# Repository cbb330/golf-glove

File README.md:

# Golf Glove
Senior Design Repository

## Firmware Quick-Reference
The Golf Glove device uses Bluetooth Low Energy (minimum BT v4.0) using the [Generic ATTribute](https://en.wikipedia.org/wiki/Bluetooth_Low_Energy#GATT_operations) (GATT) profile, an application layer protocol.

* [Golf Glove GATT Service Reference](firmware/GATT.md)

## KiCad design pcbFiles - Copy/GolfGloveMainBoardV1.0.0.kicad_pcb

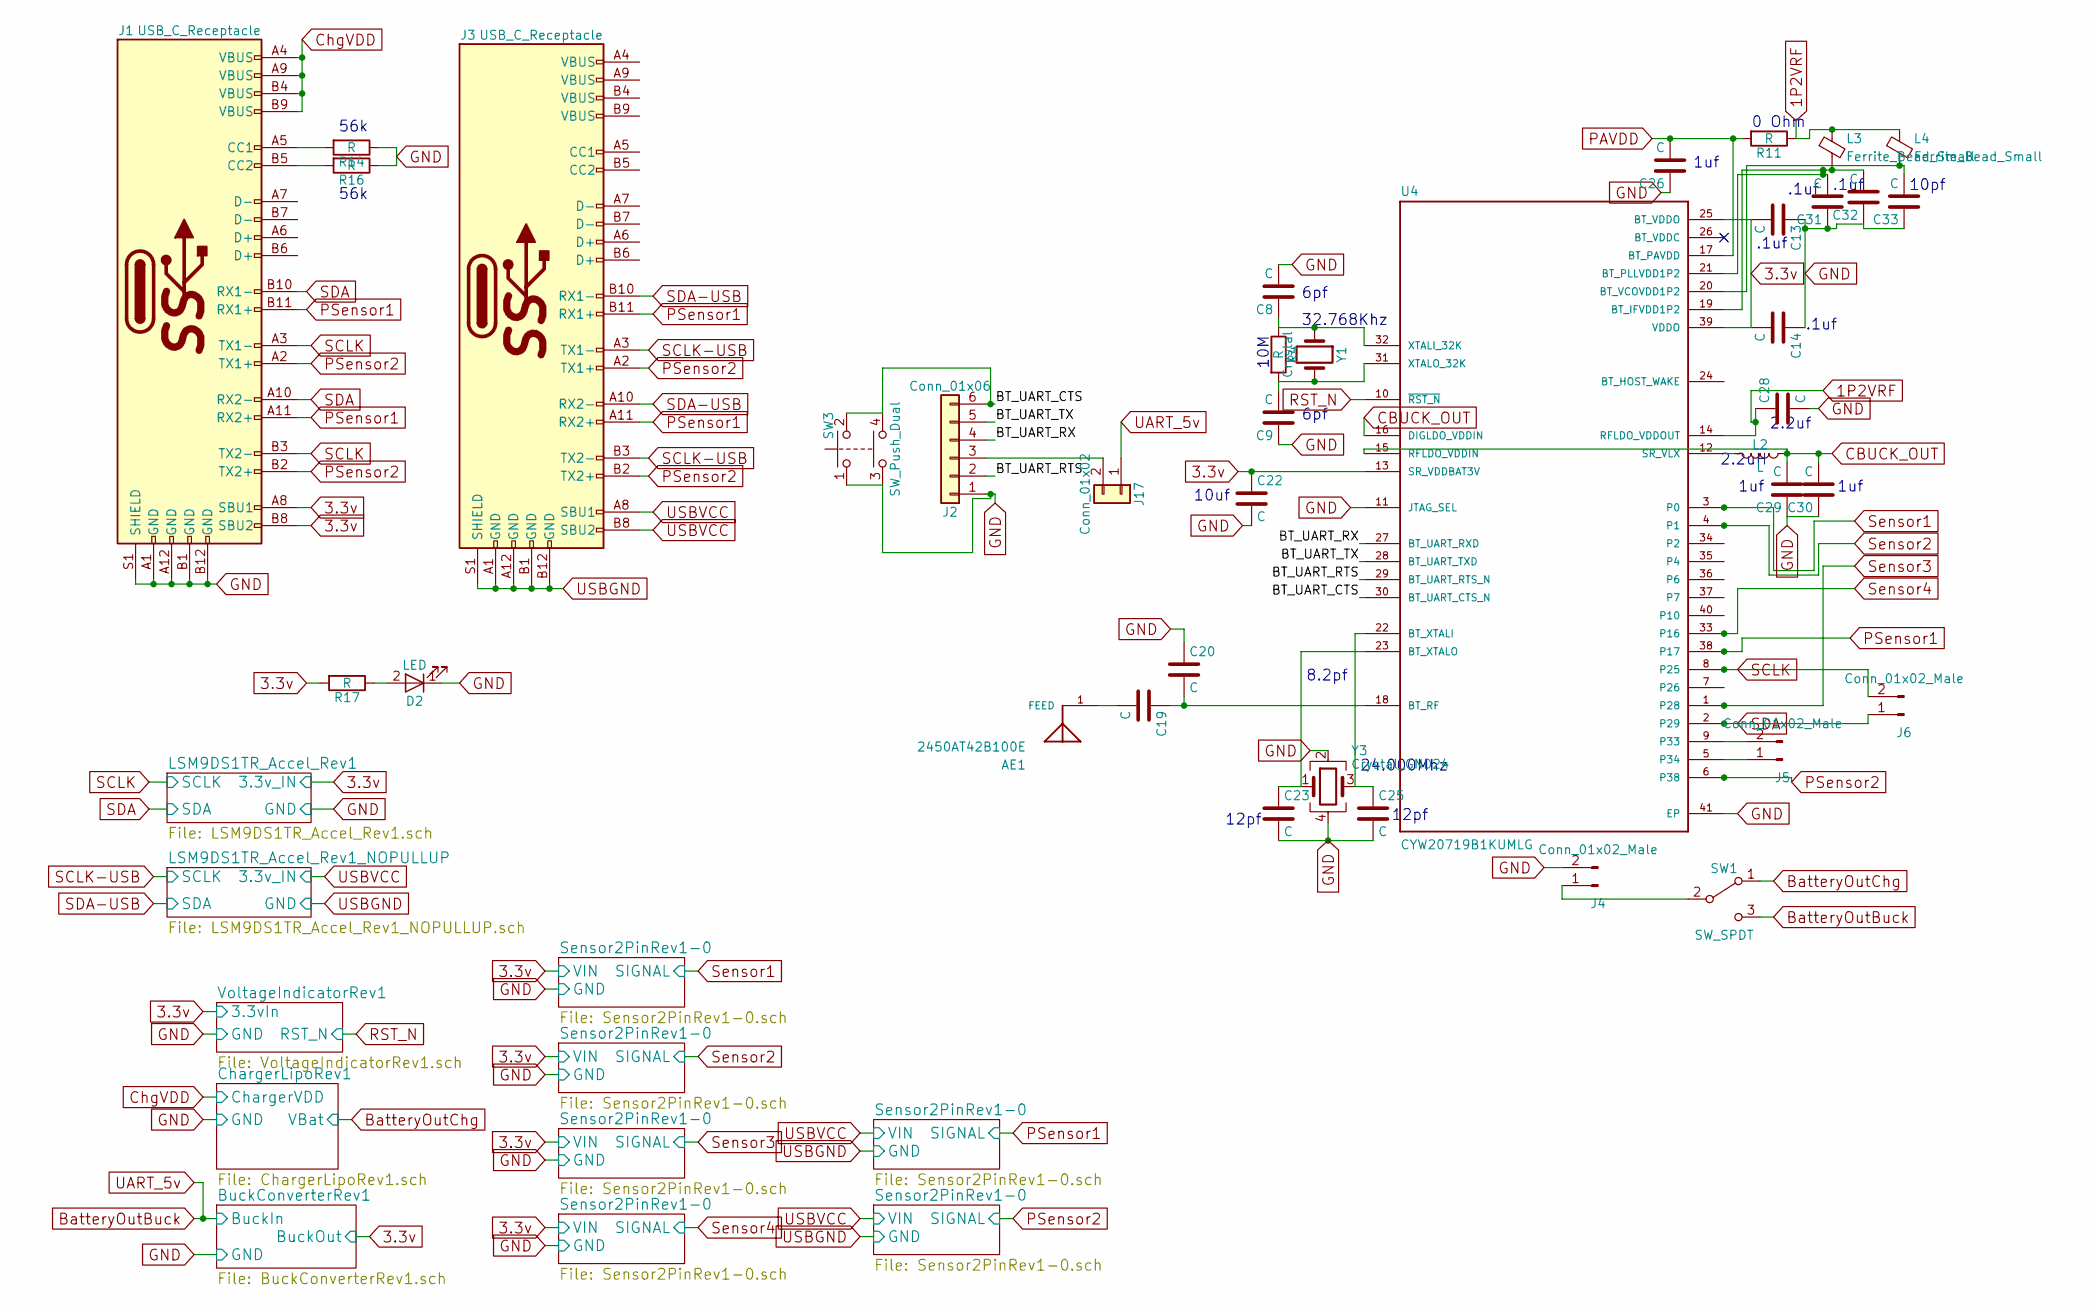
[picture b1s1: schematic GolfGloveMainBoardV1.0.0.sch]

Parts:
AE1: 2450AT42B100E; XCVR_2450AT42B100E
C8, C9, C13, C14, C19, C20, C22, C23, C25, C26, C28, C29, C30, C31, C32, C33: C; C_0402
D2: LED; C_0603
J1, J3: USB_C_Receptacle; USB_C_Receptacle_Amphenol_12401548E4-2A
J2: Conn_01x06; Pin_Header_Straight_1x06_Pitch2.54mm
J4, J5, J6: Conn_01x02_Male; Pin_Header_Straight_1x02_Pitch2.54mm
J17: Conn_01x02; Pin_Header_Straight_1x02_Pitch2.54mm
L2: L; L_0402
L3, L4: Ferrite_Bead_Small; R_0603
R4, R11, R14, R16, R17: R; R_0402
SW1: SW_SPDT; SW_SPDT_PCM12
SW3: SW_Push_Dual; SW_PUSH_6mm
U4: CYW20719B1KUMLG; QFN40P500X500X60-41N
Y1: Crystal; Crystal_SMD_3215-2pin_3.2x1.5mm
Y3: Crystal_GND24; Crystal_SMD_2016-4pin_2.0x1.6mm

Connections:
1P2VRF: C28.1, L3.1, L4.1, R11.1, U4.14 (RFLDO_VDDOUT)
3.3v: C13.2, C14.2, C22.1, J1.A8 (SBU1), J1.B8 (SBU2), R17.2, U4.13 (SR_VDDBAT3V), U4.25 (BT_VDDO), U4.39 (VDDO); also elsewhere on the board
/BT_UART_CTS: J2.6, SW3.2, SW3.4, U4.30 (BT_UART_CTS_N)
/BT_UART_RTS: J2.2, U4.29 (BT_UART_RTS_N)
/BT_UART_RX: J2.4, U4.27 (BT_UART_RXD)
/BT_UART_TX: J2.5, U4.28 (BT_UART_TXD)
BatteryOutBuck: J17.1, SW1.3 (C); also elsewhere on the board
BatteryOutChg: SW1.1 (A); also elsewhere on the board
CBUCK_OUT: C29.2, C30.2, L2.1, U4.15 (RFLDO_VDDIN), U4.16 (DIGLDO_VDDIN)
ChgVDD: J1.A4 (VBUS), J1.A9 (VBUS), J1.B4 (VBUS), J1.B9 (VBUS); also elsewhere on the board
GND: C8.2, C9.1, C13.1, C14.1, C20.1, C22.2, C23.2, C25.2, C26.1, C28.2, C29.1, C30.1, C31.1, C32.1, C33.1, D2.1 (K), J1.A1 (GND), J1.A12 (GND), J1.B1 (GND), J1.B12 (GND), J1.S1 (SHIELD), J2.1, J4.2, R14.1, R16.1, SW3.1, SW3.3, U4.11 (JTAG_SEL), U4.41 (EP), Y3.2, Y3.4; also elsewhere on the board
unnamed: AE1.1, C19.2
unnamed: C8.1, R4.1, U4.32 (XTALI_32K), Y1.1
unnamed: C9.2, R4.2, U4.31 (XTALO_32K), Y1.2
unnamed: C19.1, C20.2, U4.18 (BT_RF)
unnamed: C23.1, U4.23 (BT_XTALO), Y3.1
unnamed: C25.1, U4.22 (BT_XTALI), Y3.3
unnamed: C31.2, C32.2, L3.2, U4.19 (BT_IFVDD1P2), U4.21 (BT_PLLVDD1P2)
unnamed: C33.2, L4.2, U4.20 (BT_VCOVDD1P2)
unnamed: D2.2 (A), R17.1
unnamed: J1.A5 (CC1), R14.2
unnamed: J1.B5 (CC2), R16.2
unnamed: J4.1, SW1.2 (B)
unnamed: J5.1, U4.5 (P34)
unnamed: J5.2, U4.9 (P33)
unnamed: J2.3, J17.2
unnamed: L2.2, U4.12 (SR_VLX)
PAVDD: C26.2, R11.2, U4.17 (BT_PAVDD)
PSensor1: J1.A11 (RX2+), J1.B11 (RX1+), J3.A11 (RX2+), J3.B11 (RX1+), U4.38 (P17); also elsewhere on the board
PSensor2: J1.A2 (TX1+), J1.B2 (TX2+), J3.A2 (TX1+), J3.B2 (TX2+), U4.6 (P38); also elsewhere on the board
SCLK: J1.A3 (TX1-), J1.B3 (TX2-), J6.2, U4.8 (P25); also elsewhere on the board
SCLK-USB: J3.A3 (TX1-), J3.B3 (TX2-); also elsewhere on the board
SDA: J1.A10 (RX2-), J1.B10 (RX1-), J6.1, U4.2 (P29); also elsewhere on the board
SDA-USB: J3.A10 (RX2-), J3.B10 (RX1-); also elsewhere on the board
Sensor1: U4.3 (P0); also elsewhere on the board
Sensor2: U4.4 (P1); also elsewhere on the board
Sensor3: U4.1 (P28); also elsewhere on the board
Sensor4: U4.33 (P16); also elsewhere on the board
USBGND: J3.A1 (GND), J3.A12 (GND), J3.B1 (GND), J3.B12 (GND), J3.S1 (SHIELD); also elsewhere on the board
USBVCC: J3.A8 (SBU1), J3.B8 (SBU2); also elsewhere on the board

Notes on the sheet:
8.2pf
12pf
10uf
6pf
1uf
.1uf
10pf
2.2uf
2.2uH
0 Ohm
10M
32.768Khz
24.000Mhz
56k

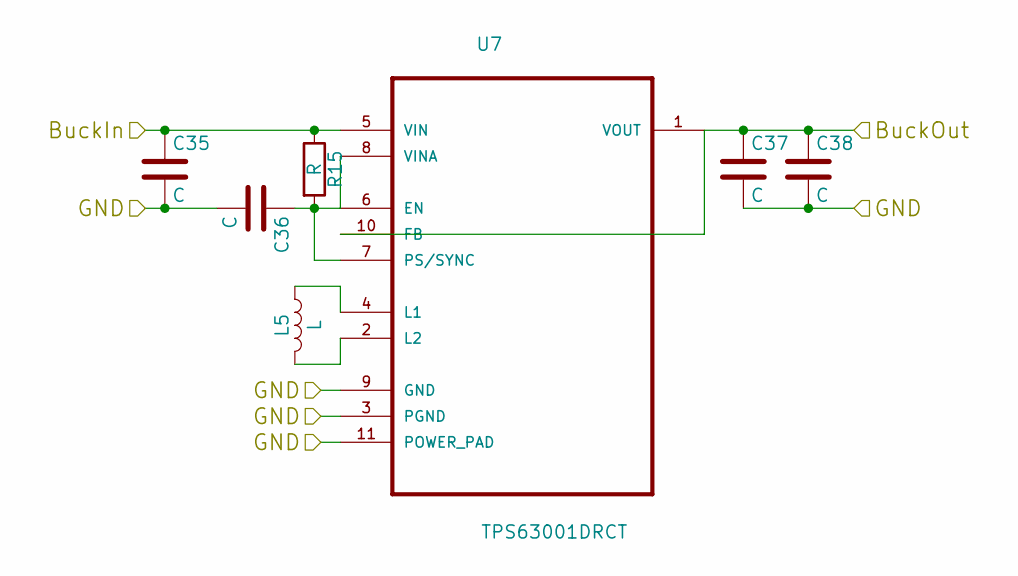
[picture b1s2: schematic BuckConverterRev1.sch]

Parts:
C35, C36, C37, C38: C; C_0402
L5: L; L_0603
R15: R; R_0402
U7: TPS63001DRCT; SON50P300X300X100-11N

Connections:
BatteryOutBuck: C35.1, R15.1, U7.5 (VIN); also elsewhere on the board
GND: C35.2, C36.2, C37.2, C38.2, U7.3 (PGND), U7.9 (GND), U7.11 (POWER_PAD); also elsewhere on the board
unnamed: C36.1, R15.2, U7.6 (EN), U7.7 (PS/SYNC), U7.8 (VINA)
unnamed 25: C37.1, C38.1, U7.1 (VOUT), U7.10 (FB); also elsewhere on the board
unnamed: L5.1, U7.4 (L1)
unnamed: L5.2, U7.2 (L2)

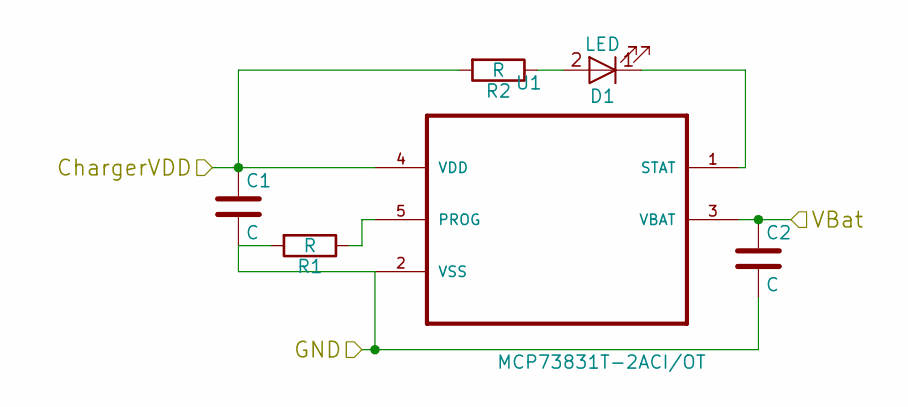
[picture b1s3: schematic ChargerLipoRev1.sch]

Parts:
C1, C2: C; C_0402
D1: LED; C_0603
R1, R2: R; R_0402
U1: MCP73831T-2ACI/OT; SOT95P280X145-5N

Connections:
BatteryOutChg: C2.1, U1.3 (VBAT); also elsewhere on the board
ChgVDD: C1.1, R2.2, U1.4 (VDD); also elsewhere on the board
GND: C1.2, C2.2, R1.2, U1.2 (VSS); also elsewhere on the board
unnamed: D1.1 (K), U1.1 (STAT)
unnamed: D1.2 (A), R2.1
unnamed: R1.1, U1.5 (PROG)

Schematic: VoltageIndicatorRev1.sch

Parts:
C3, C4: C; C_0402
J6: Screw_Terminal_01x02; Pin_Header_Straight_1x02_Pitch2.54mm
R3: R; R_0402
SW2: SW_Push; SW_DIP_x1_W8.61mm_Slide_LowProfile
U2: XC6119N16A7R-G; DFN-4

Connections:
3.3v: R3.1; also elsewhere on the board
GND: C3.2, C4.1, SW2.1, U2.3 (VSS); also elsewhere on the board
unnamed: C3.1, U2.2 (Cd/NC)

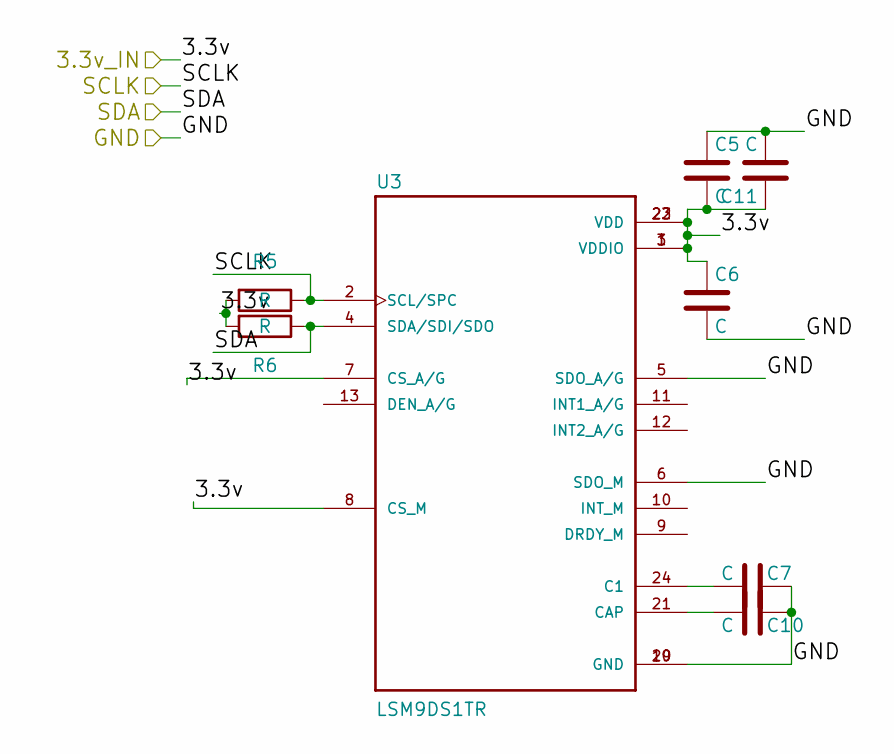
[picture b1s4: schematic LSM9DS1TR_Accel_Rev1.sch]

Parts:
C5, C6, C7, C10, C11: C; C_0402
R5, R6: R; R_0402
U3: LSM9DS1TR; PQFN43P300X350X102-24N

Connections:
3.3v: C5.2, C6.1, C11.1, R5.2, R6.2, U3.1 (VDDIO), U3.3 (VDDIO), U3.7 (CS_A/G), U3.8 (CS_M), U3.22 (VDD), U3.23 (VDD); also elsewhere on the board
GND: C5.1, C6.2, C7.1, C10.1, C11.2, U3.5 (SDO_A/G), U3.6 (SDO_M), U3.19 (GND), U3.20 (GND); also elsewhere on the board
unnamed: C7.2, U3.24 (C1)
unnamed: C10.2, U3.21 (CAP)
SCLK: R5.1, U3.2 (SCL/SPC); also elsewhere on the board
SDA: R6.1, U3.4 (SDA/SDI/SDO); also elsewhere on the board

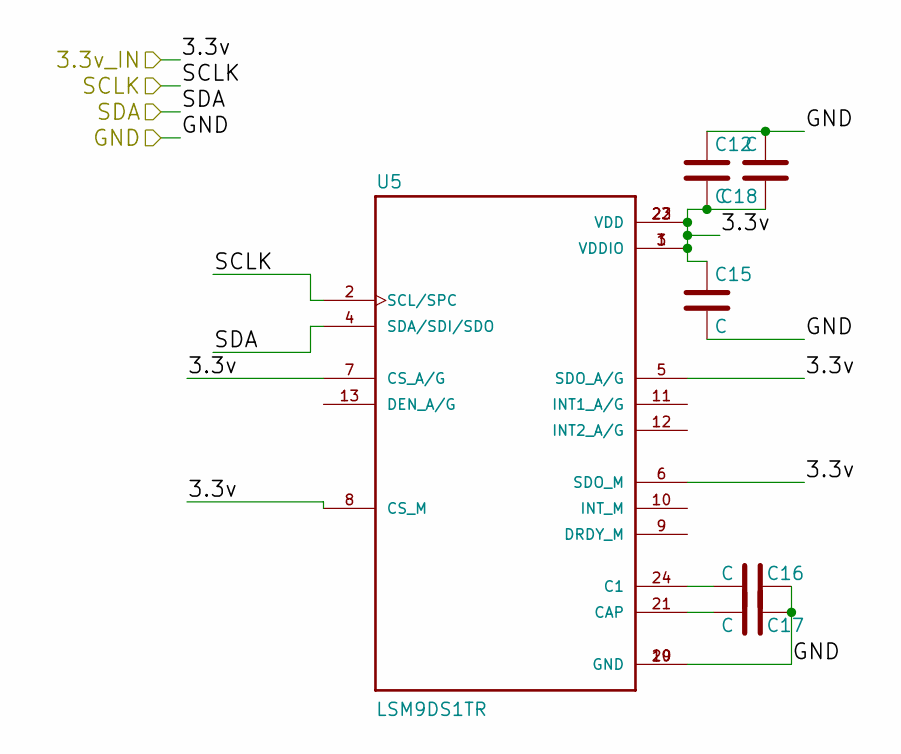
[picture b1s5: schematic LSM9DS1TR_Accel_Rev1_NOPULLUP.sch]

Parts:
C12, C15, C16, C17, C18: C; C_0402
U5: LSM9DS1TR; PQFN43P300X350X102-24N

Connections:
unnamed: C16.2, U5.24 (C1)
unnamed: C17.2, U5.21 (CAP)
SCLK-USB: U5.2 (SCL/SPC); also elsewhere on the board
SDA-USB: U5.4 (SDA/SDI/SDO); also elsewhere on the board
USBGND: C12.1, C15.2, C16.1, C17.1, C18.2, U5.19 (GND), U5.20 (GND); also elsewhere on the board
USBVCC: C12.2, C15.1, C18.1, U5.1 (VDDIO), U5.3 (VDDIO), U5.5 (SDO_A/G), U5.6 (SDO_M), U5.7 (CS_A/G), U5.8 (CS_M), U5.22 (VDD), U5.23 (VDD); also elsewhere on the board

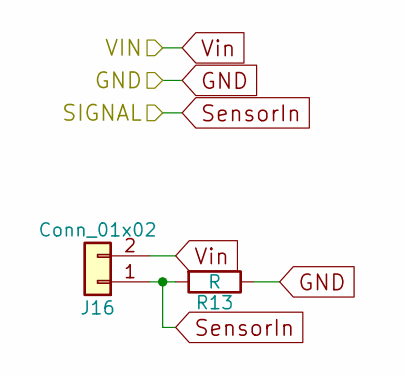
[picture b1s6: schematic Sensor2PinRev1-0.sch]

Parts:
J7: Conn_01x02; Pin_Header_Straight_1x02_Pitch2.54mm
R7: R; R_0402

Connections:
3.3v: J7.2; also elsewhere on the board
GND: R7.1; also elsewhere on the board
Sensor1: J7.1, R7.2; also elsewhere on the board

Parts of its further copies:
J8, J9, J14, J15, J16: Conn_01x02; Pin_Header_Straight_1x02_Pitch2.54mm
R8, R9, R10, R12, R13: R; R_0402

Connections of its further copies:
3.3v: J8.2, J9.2, J14.2; also elsewhere on the board
GND: R8.1, R9.1, R10.1; also elsewhere on the board
PSensor1: J15.1, R12.2; also elsewhere on the board
PSensor2: J16.1, R13.2; also elsewhere on the board
Sensor2: J8.1, R8.2; also elsewhere on the board
Sensor3: J9.1, R9.2; also elsewhere on the board
Sensor4: J14.1, R10.2; also elsewhere on the board
USBGND: R12.1, R13.1; also elsewhere on the board
USBVCC: J15.2, J16.2; also elsewhere on the board

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
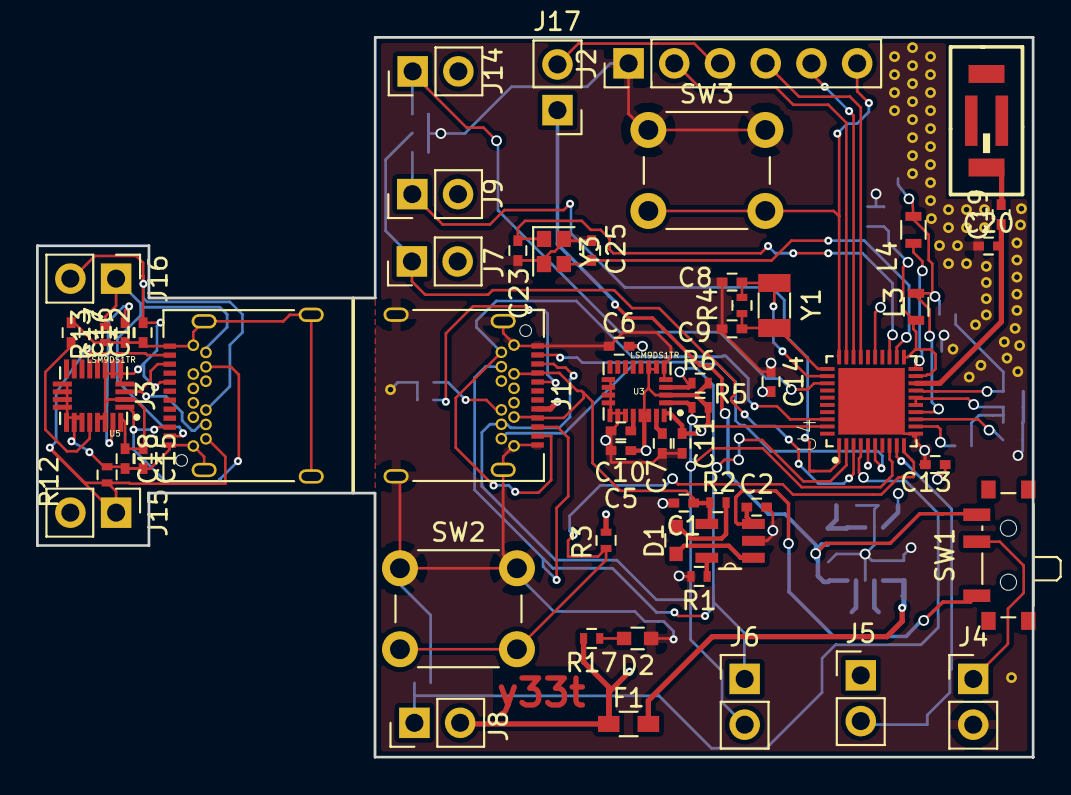
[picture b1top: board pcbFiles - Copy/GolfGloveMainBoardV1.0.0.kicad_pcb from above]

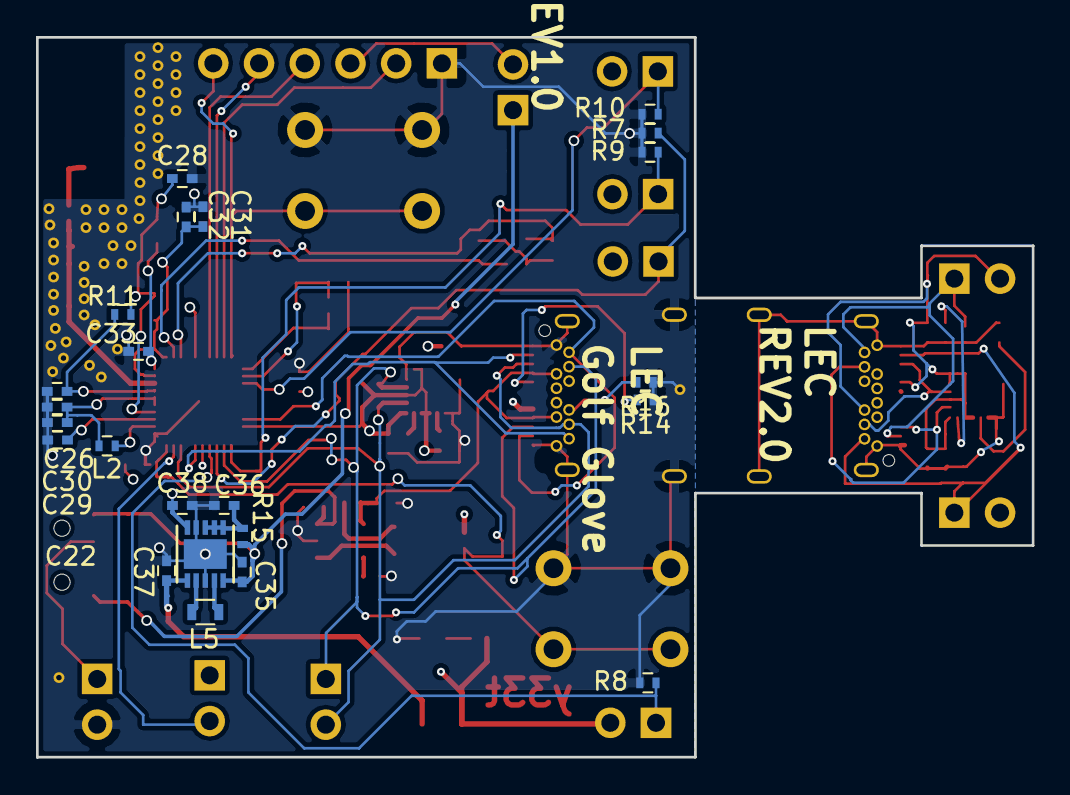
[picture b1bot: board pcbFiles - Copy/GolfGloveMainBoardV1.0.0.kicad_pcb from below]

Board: 4 copper layers, 55.3 x 40.0 mm, 80 parts (23 on the bottom side), 52 nets.

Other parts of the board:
F1: Polyfuse; R_0603_HandSoldering

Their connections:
3.3v: F1.1; also elsewhere on the board
unnamed 25: F1.2; also elsewhere on the board

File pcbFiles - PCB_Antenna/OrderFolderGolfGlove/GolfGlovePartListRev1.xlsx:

PartName | Value | Form Factor | Part Number | Brand | Price | Type | Link
C3 | .033uF | 402 |  |  |  | CAP | https://www.digikey.com/product-detail/en/kemet/C0402C333J4R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
C13 | .1uF | 402 |  |  |  | CAP | https://www.digikey.com/product-detail/en/samsung-electro-me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
C14 | .1uF | 402 |  |  |  | CAP | https://www.digikey.com/product-detail/en/samsung-electro-me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
C31 | .1uF | 402 |  |  |  | CAP | https://www.digikey.com/product-detail/en/samsung-electro-me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
C32 | .1uF | 402 |  |  |  | CAP | https://www.digikey.com/product-detail/en/samsung-electro-me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
C4 | .1uF | 402 |  |  |  | CAP | https://www.digikey.com/product-detail/en/samsung-electro-me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
C36 | .1uF | 402 |  |  |  | CAP | https://www.digikey.com/product-detail/en/samsung-electro-me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
C12 | 100nF | 402 |  |  |  | CAP | https://www.digikey.com/product-detail/en/samsung-electro-me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
C15 | 100nF | 402 |  |  |  | CAP | https://www.digikey.com/product-detail/en/samsung-electro-me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
C16 | 100nF | 402 |  |  |  | CAP | https://www.digikey.com/product-detail/en/samsung-electro-me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
C5 | 100nF | 402 |  |  |  | CAP | https://www.digikey.com/product-detail/en/samsung-electro-me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
C6 | 100nF | 402 |  |  |  | CAP | https://www.digikey.com/product-detail/en/samsung-electro-me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
C7 | 100nF | 402 |  |  |  | CAP | https://www.digikey.com/product-detail/en/samsung-electro-me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
C10 | 10nF (16V) | 402 |  |  |  | CAP | https://www.digikey.com/product-detail/en/murata-electronics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
C17 | 10nF (16V) | 402 |  |  |  | CAP | https://www.digikey.com/product-detail/en/murata-electronics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
C33 | 10pF | 402 |  |  |  | CAP | https://www.digikey.com/product-detail/en/murata-electronics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
C1 | 10uF | 402 |  |  |  | CAP | https://www.digikey.com/product-detail/en/murata-electronics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
C11 | 10uF | 402 |  |  |  | CAP | https://www.digikey.com/product-detail/en/murata-electronics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
C18 | 10uF | 402 |  |  |  | CAP | https://www.digikey.com/product-detail/en/murata-electronics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
C2 | 10uF | 402 |  |  |  | CAP | https://www.digikey.com/product-detail/en/murata-electronics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
C22 | 10uF | 402 |  |  |  | CAP | https://www.digikey.com/product-detail/en/murata-electronics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
C35 | 10uF | 402 |  |  |  | CAP | https://www.digikey.com/product-detail/en/murata-electronics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
C37 | 10uF | 402 |  |  |  | CAP | https://www.digikey.com/product-detail/en/murata-electronics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
C38 | 10uF | 402 |  |  |  | CAP | https://www.digikey.com/product-detail/en/murata-electronics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
C23 | 12pF | 402 |  |  |  | CAP | https://www.digikey.com/product-detail/en/samsung-electro-me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
C25 | 12pF | 402 |  |  |  | CAP | https://www.digikey.com/product-detail/en/samsung-electro-me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
C26 | 1uF | 402 |  |  |  | CAP | https://www.digikey.com/product-detail/en/samsung-electro-me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
C29 | 1uF | 402 |  |  |  | CAP | https://www.digikey.com/product-detail/en/samsung-electro-me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
C30 | 1uF | 402 |  |  |  | CAP | https://www.digikey.com/product-detail/en/samsung-electro-me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
C28 | 2.2uF | 402 |  |  |  | CAP | https://www.digikey.com/product-detail/en/murata-electronics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
C8 | 6pF | 402 |  |  |  | CAP | https://www.digikey.com/product-detail/en/yageo/CC0402DRNPO9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
C9 | 6pF | 402 |  |  |  | CAP | https://www.digikey.com/product-detail/en/yageo/CC0402DRNPO9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
D1 | blue LED | 603 |  | Kingbright |  | LED | https://www.digikey.com/product-detail/en/kingbright/APTD160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
J1 | USB-C | USB-C |  |  |  | CONNECTOR | https://www.ttiinc.com/content/ttiinc/en/apps/part-detail.ht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
J11 | N/A |  |  |  |  | HEADER | N/A
J12 | N/A |  |  |  |  | HEADER | N/A
J13 | N/A |  |  |  |  | HEADER | N/A
J14 | N/A |  |  |  |  | HEADER | N/A
J15 | N/A |  |  |  |  | HEADER | N/A
J16 | N/A |  |  |  |  | HEADER | N/A
J17 | N/A |  |  |  |  | HEADER | N/A
J2 | N/A |  |  |  |  | HEADER | N/A
J3 | USB-C | USB-C |  |  |  | CONNECTOR | https://www.ttiinc.com/content/ttiinc/en/apps/part-detail.ht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
J6 | N/A |  |  |  |  | HEADER | N/A
J7 | N/A |  |  |  |  | HEADER | N/A
J8 | N/A |  |  |  |  | HEADER | N/A
J9 | N/A |  |  |  |  | HEADER | N/A
L1 |  | 402 |  |  |  | INDUCTOR
L2 | 2.2uH | 402 |  |  |  | INDUCTOR | https://www.digikey.com/product-detail/en/tdk-corporation/ML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
L3 | 600@100MHz | 603 |  |  |  | FERRITE BEAD | https://www.digikey.com/product-detail/en/wurth-electronics-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
L4 | 600@100MHz | 603 |  |  |  | FERRITE BEAD | https://www.digikey.com/product-detail/en/wurth-electronics-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
L5 | 2.2uH | 603 |  |  |  | INDUCTOR | https://www.digikey.com/product-detail/en/tdk-corporation/ML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
L6 |  | 402 |  |  |  | INDUCTOR
R11 | 0 | 402 |  |  |  | RESISTOR | https://www.digikey.com/product-detail/en/stackpole-electron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
R15 | 100 | 402 |  |  |  | RESISTOR | https://www.digikey.com/product-detail/en/panasonic-electron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
R2 | 470 | 402 |  |  |  | RESISTOR | https://www.digikey.com/product-detail/en/panasonic-electron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
R5 | 10K | 402 |  |  |  | RESISTOR | https://www.digikey.com/product-detail/en/susumu/RR0510P-103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
R6 | 10K | 402 |  |  |  | RESISTOR | https://www.digikey.com/product-detail/en/susumu/RR0510P-103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
R4 | 10M | 402 |  |  |  | RESISTOR | https://www.digikey.com/product-detail/en/te-connectivity-pa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
R10 | 13.5K | 402 |  |  |  | RESISTOR | https://www.digikey.com/product-detail/en/vishay-dale/TNPW04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
R12 | 13.5K | 402 |  |  |  | RESISTOR | https://www.digikey.com/product-detail/en/vishay-dale/TNPW04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
R13 | 13.5K | 402 |  |  |  | RESISTOR | https://www.digikey.com/product-detail/en/vishay-dale/TNPW04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
R7 | 13.5K | 402 |  |  |  | RESISTOR | https://www.digikey.com/product-detail/en/vishay-dale/TNPW04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
R8 | 13.5K | 402 |  |  |  | RESISTOR | https://www.digikey.com/product-detail/en/vishay-dale/TNPW04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
R9 | 13.5K | 402 |  |  |  | RESISTOR | https://www.digikey.com/product-detail/en/vishay-dale/TNPW04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
R1 | 2k | 402 |  |  |  | RESISTOR | https://www.digikey.com/product-detail/en/yageo/RT0402BRD072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
R3 | 5.6k | 402 |  |  |  | RESISTOR | https://www.digikey.com/product-detail/en/panasonic-electron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
SW1 | SPDT PCM12 | N/A |  |  |  | SWITCH | https://www.digikey.com/product-detail/en/c-k/PCM12SMTR/401-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
SW2 | SW_DIP_x1_W8.61mm_Slide_LowProfile | N/A |  |  |  | SWITCH | https://www.digikey.com/product-detail/en/nidec-copal-electr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
U1 | N/A | N/A | MCP73831T | Microchip |  | CHARGER | https://www.digikey.com/product-detail/en/microchip-technolo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
U2 | N/A | N/A | XC6119N16A7R-G | Torex |  |  | https://www.digikey.com/product-detail/en/torex-semiconducto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
U3 | N/A | N/A | LSM9DS1TR | STMicroelectronics |  | ACCELEROMETER | https://www.digikey.com/product-detail/en/stmicroelectronics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
U4 | N/A | N/A | CYW20719B1KUMLG | Cypress |  | MICROCONTROLLER | https://www.digikey.com/products/en?keywords=CYW20719B1KUMLG
U5 | N/A | N/A | LSM9DS1TR | STMicroelectronics |  | ACCELEROMETER | https://www.digikey.com/product-detail/en/stmicroelectronics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
U7 | N/A | N/A | TPS63001DRCT | TexasInstruments |  | BUCK/BOOST | https://www.digikey.com/product-detail/en/texas-instruments/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
Y1 | 32.768Khz | 0603 2pin |  |  |  | CRYSTAL | https://www.digikey.com/product-detail/en/epson/FC-135-32.76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
Y2 | 24.000Mhz | 0603 3pin |  |  |  | CRYSTAL | https://www.digikey.com/product-detail/en/murata-electronics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

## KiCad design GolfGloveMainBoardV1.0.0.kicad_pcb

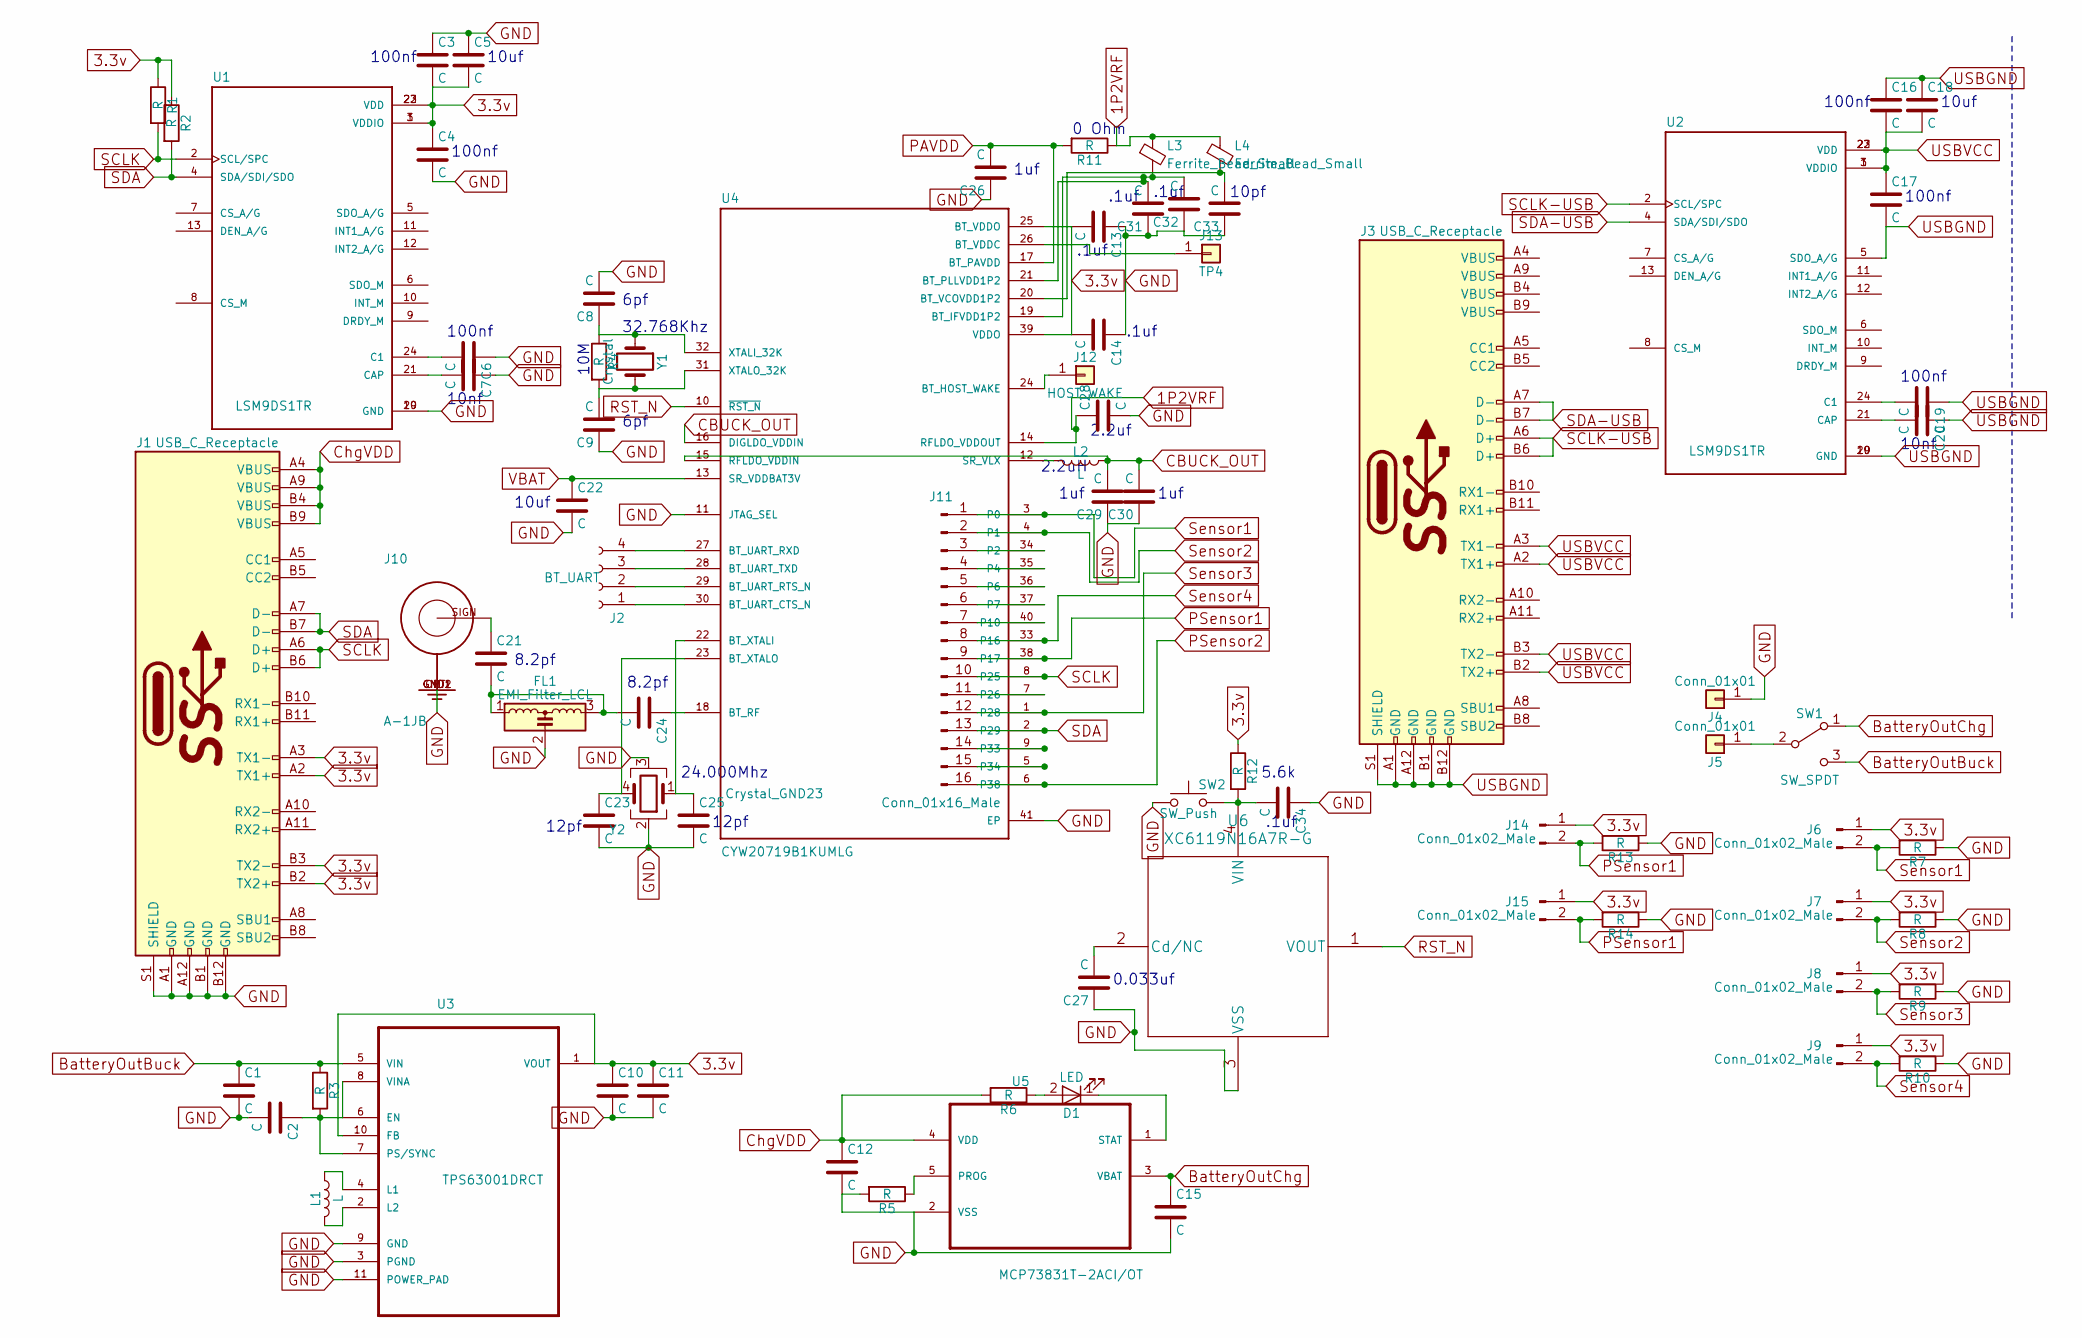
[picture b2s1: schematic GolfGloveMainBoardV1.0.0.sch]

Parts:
C1, C2, C3, C4, C5, C6, C7, C8, C9, C10, C11, C12, C13, C14, C15, C16, C17, C18, C19, C20, C21, C22, C23, C24, C25, C26, C27, C28, C29, C30, C31, C32, C33, C34: C; C_0402
D1: LED; LED_0603
FL1: EMI_Filter_LCL; R_0603
J1, J3: USB_C_Receptacle; USB_C_Receptacle_Amphenol_12401548E4-2A
J2: BT_UART; Socket_Strip_Straight_1x04_Pitch2.54mm
J4, J5: Conn_01x01; SolderWirePad_single_2mmDrill
J6, J7, J8, J9, J14, J15: Conn_01x02_Male; Pin_Header_Straight_1x02_Pitch2.54mm
J10: A-1JB; AMPHENOL_A-1JB
J11: Conn_01x16_Male; Pin_Header_Straight_2x08_Pitch2.54mm
J12: HOST_WAKE; Pin_Header_Straight_1x01_Pitch2.54mm
J13: TP4; Pin_Header_Straight_1x01_Pitch2.54mm
L1, L2: L; L_0805
L3, L4: Ferrite_Bead_Small; R_0603
R1, R2, R3, R4, R5, R6, R7, R8, R9, R10, R11, R12, R13, R14: R; C_0603
SW1: SW_SPDT; SDTPSwitchAmazon
SW2: SW_Push; SW_SPST_B3S-1000
U1, U2: LSM9DS1TR; PQFN43P300X350X102-24N
U3: TPS63001DRCT; SON50P300X300X100-11N
U4: CYW20719B1KUMLG; QFN40P500X500X60-41N
U5: MCP73831T-2ACI/OT; SOT95P280X145-5N
U6: XC6119N16A7R-G; DFN-4
Y1: Crystal; Crystal_SMD_0603-2pin_6.0x3.5mm_HandSoldering
Y2: Crystal_GND23; Crystal_SMD_0603-4pin_6.0x3.5mm_HandSoldering

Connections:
1P2VRF: C28.1, L3.1, L4.1, R11.1, U4.14 (RFLDO_VDDOUT)
3.3v: C3.2, C4.1, C5.2, C10.1, C11.1, C13.2, C14.2, J1.A2 (TX1+), J1.A3 (TX1-), J1.B2 (TX2+), J1.B3 (TX2-), J6.1, J7.1, J8.1, J9.1, J14.1, J15.1, R1.1, R2.1, R12.1, U1.1 (VDDIO), U1.3 (VDDIO), U1.22 (VDD), U1.23 (VDD), U3.1 (VOUT), U3.10 (FB), U4.25 (BT_VDDO), U4.39 (VDDO)
BatteryOutBuck: C1.1, R3.1, SW1.3 (C), U3.5 (VIN)
BatteryOutChg: C15.1, SW1.1 (A), U5.3 (VBAT)
CBUCK_OUT: C29.2, C30.2, L2.1, U4.15 (RFLDO_VDDIN), U4.16 (DIGLDO_VDDIN)
ChgVDD: C12.1, J1.A4 (VBUS), J1.A9 (VBUS), J1.B4 (VBUS), J1.B9 (VBUS), R6.2, U5.4 (VDD)
GND: C1.2, C2.2, C3.1, C4.2, C5.1, C6.1, C7.1, C8.2, C9.1, C10.2, C11.2, C12.2, C13.1, C14.1, C15.2, C22.2, C23.2, C25.2, C26.1, C27.1, C28.2, C29.1, C30.1, C31.1, C32.1, C33.1, C34.1, FL1.2, J1.A1 (GND), J1.A12 (GND), J1.B1 (GND), J1.B12 (GND), J1.S1 (SHIELD), J4.1, J10.GND1 (GND), J10.GND2 (GND), J10.OPTI (GND), R5.2, R7.1, R8.1, R9.1, R10.1, R13.1, R14.1, SW2.1, U1.19 (GND), U1.20 (GND), U3.3 (PGND), U3.9 (GND), U3.11 (POWER_PAD), U4.11 (JTAG_SEL), U4.41 (EP), U5.2 (VSS), U6.3 (VSS), Y2.2, Y2.3
unnamed: C2.1, R3.2, U3.6 (EN), U3.7 (PS/SYNC), U3.8 (VINA)
unnamed: C6.2, U1.24 (C1)
unnamed: C7.2, U1.21 (CAP)
unnamed: C8.1, R4.1, U4.32 (XTALI_32K), Y1.1
unnamed: C9.2, R4.2, U4.31 (XTALO_32K), Y1.2
unnamed: C19.2, U2.24 (C1)
unnamed: C20.2, U2.21 (CAP)
unnamed: C21.1, J10.SIGN (SIGNAL)
unnamed: C21.2, C24.2, FL1.1, FL1.3
unnamed: C23.1, U4.23 (BT_XTALO), Y2.4
unnamed: C24.1, U4.18 (BT_RF)
unnamed: C25.1, U4.22 (BT_XTALI), Y2.1
unnamed: C27.2, U6.2 (Cd/NC)
unnamed: C31.2, C32.2, L3.2, U4.19 (BT_IFVDD1P2), U4.21 (BT_PLLVDD1P2)
unnamed: C33.2, L4.2, U4.20 (BT_VCOVDD1P2)
unnamed: C34.2, R12.2, SW2.2, U6.4 (VIN)
unnamed: D1.1 (K), U5.1 (STAT)
unnamed: D1.2 (A), R6.1
unnamed: J2.1, U4.30 (BT_UART_CTS_N)
unnamed: J2.2, U4.29 (BT_UART_RTS_N)
unnamed: J2.3, U4.28 (BT_UART_TXD)
unnamed: J2.4, U4.27 (BT_UART_RXD)
unnamed: J5.1, SW1.2 (B)
unnamed: J11.3, U4.34 (P2)
unnamed: J11.4, U4.35 (P4)
unnamed: J11.5, U4.36 (P6)
unnamed: J11.6, U4.37 (P7)
unnamed: J11.7, U4.40 (P10)
unnamed: J11.11, U4.7 (P26)
unnamed: J11.14, U4.9 (P33)
unnamed: J11.15, U4.5 (P34)
unnamed: J12.1, U4.24 (BT_HOST_WAKE)
unnamed: J13.1, U4.26 (BT_VDDC)
unnamed: L1.1, U3.4 (L1)
unnamed: L1.2, U3.2 (L2)
unnamed: L2.2, U4.12 (SR_VLX)
unnamed: R5.1, U5.5 (PROG)
PAVDD: C26.2, R11.2, U4.17 (BT_PAVDD)
PSensor1: J11.9, J14.2, J15.2, R13.2, R14.2, U4.38 (P17)
PSensor2: J11.16, U4.6 (P38)
RST_N: U4.10 (~RST_N~), U6.1 (VOUT)
SCLK: J1.A6 (D+), J1.B6 (D+), J11.10, R1.2, U1.2 (SCL/SPC), U4.8 (P25)
SCLK-USB: J3.A6 (D+), J3.B6 (D+), U2.2 (SCL/SPC)
SDA: J1.A7 (D-), J1.B7 (D-), J11.13, R2.2, U1.4 (SDA/SDI/SDO), U4.2 (P29)
SDA-USB: J3.A7 (D-), J3.B7 (D-), U2.4 (SDA/SDI/SDO)
Sensor1: J6.2, J11.1, R7.2, U4.3 (P0)
Sensor2: J7.2, J11.2, R8.2, U4.4 (P1)
Sensor3: J8.2, J11.12, R9.2, U4.1 (P28)
Sensor4: J9.2, J11.8, R10.2, U4.33 (P16)
USBGND: C16.1, C17.2, C18.1, C19.1, C20.1, J3.A1 (GND), J3.A12 (GND), J3.B1 (GND), J3.B12 (GND), J3.S1 (SHIELD), U2.5 (SDO_A/G), U2.19 (GND), U2.20 (GND)
USBVCC: C16.2, C17.1, C18.2, J3.A2 (TX1+), J3.A3 (TX1-), J3.B2 (TX2+), J3.B3 (TX2-), U2.1 (VDDIO), U2.3 (VDDIO), U2.22 (VDD), U2.23 (VDD)
VBAT: C22.1, U4.13 (SR_VDDBAT3V)

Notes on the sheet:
100nf
10nf
10uf
8.2pf
12pf
6pf
1uf
.1uf
10pf
2.2uf
2.2uH
0 Ohm
10M
32.768Khz
24.000Mhz
5.6k
0.033uf

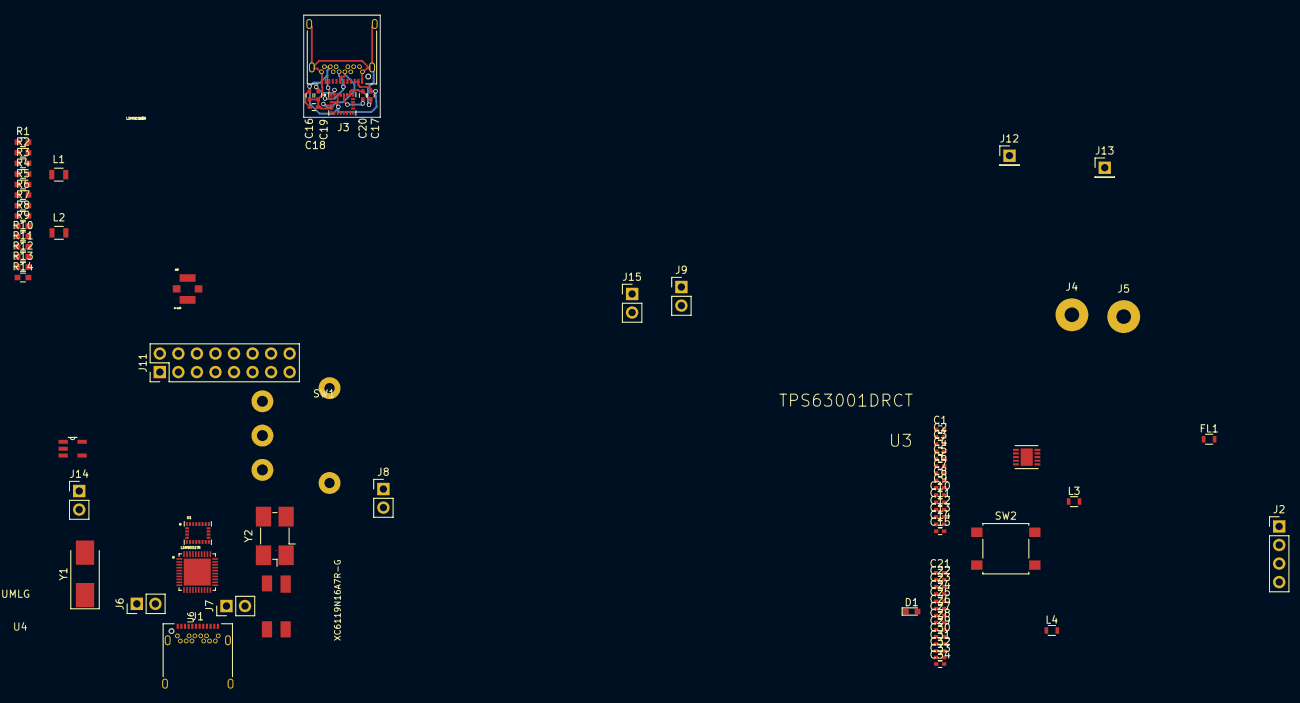
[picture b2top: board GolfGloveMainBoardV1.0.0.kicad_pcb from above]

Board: 2 copper layers, 79 parts (0 on the bottom side), 59 nets.
